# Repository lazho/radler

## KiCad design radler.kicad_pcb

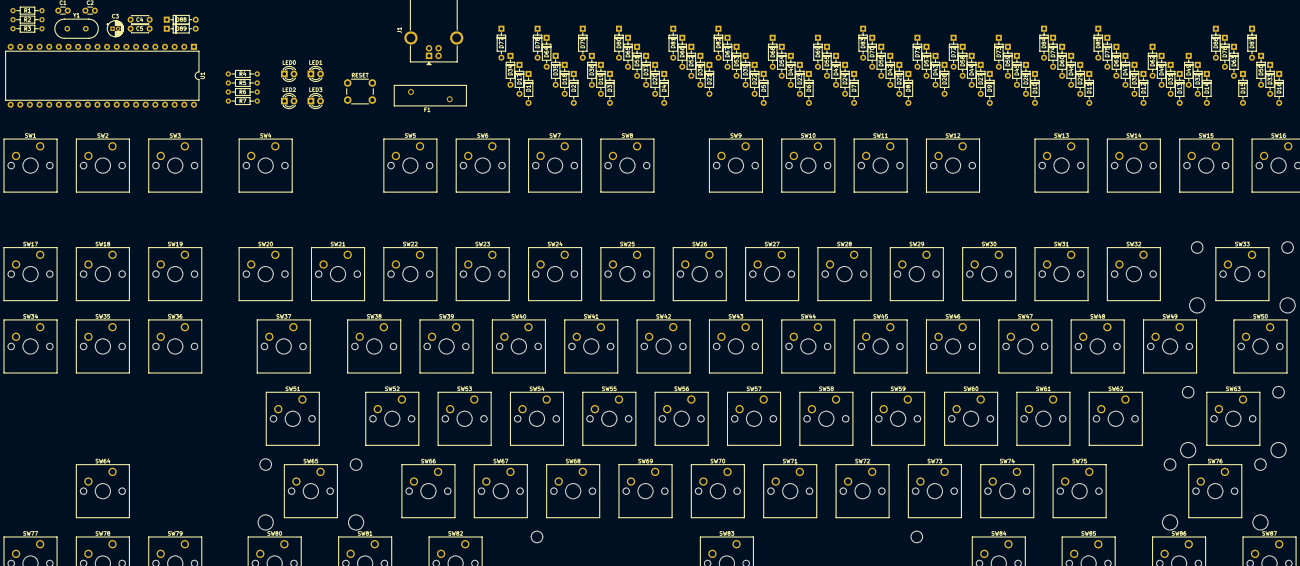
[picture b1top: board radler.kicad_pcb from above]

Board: 2 copper layers, 197 parts (0 on the bottom side), 128 nets, no tracks yet.

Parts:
C1, C2: 20p; C_Disc_D3.0mm_W1.6mm_P2.50mm
C3: 4.7u; CP_Radial_D4.0mm_P1.50mm
C4, C5: 0.1u; C_Disc_D4.3mm_W1.9mm_P5.00mm
D1, D2, D3, D4, D5, D6, D7, D8, D9, D10, D11, D12, D13, D14, D15, D16, D17, D18, D19, D20, D21, D22, D23, D24, D25, D26, D27, D28, D29, D30, D31, D32, D33, D34, D35, D36, D37, D38, D39, D40, D41, D42, D43, D44, D45, D46, D47, D48, D49, D50, D51, D52, D53, D54, D55, D56, D57, D58, D59, D60, D61, D62, D63, D64, D65, D66, D67, D68, D69, D70, D71, D72, D73, D74, D75, D76, D77, D78, D79, D80, D81, D82, D83, D84, D85, D86, D87: 1N4148; D_DO-35_SOD27_P7.62mm_Horizontal
D88, D89: 3.6V; D_DO-35_SOD27_P7.62mm_Horizontal
F1: 100mA; Fuse_BelFuse_0ZRE0100FF_L18.7mm_W5.1mm
J1: USB_B_Mini; USB_B_OST_USB-B1HSxx_Horizontal
LED0: A; LED_D3.0mm
LED1: B; LED_D3.0mm
LED2: C; LED_D3.0mm
LED3: D; LED_D3.0mm
R1, R4, R5, R6, R7: 1.5k; R_Axial_DIN0204_L3.6mm_D1.6mm_P7.62mm_Horizontal
R2, R3: 68; R_Axial_DIN0204_L3.6mm_D1.6mm_P7.62mm_Horizontal
RESET: RESET; SW_PUSH_6mm
SW1: Pause; SW_Cherry_MX_1.00u_PCB
SW2: ScrLk; SW_Cherry_MX_1.00u_PCB
SW3: PrtSc; SW_Cherry_MX_1.00u_PCB
SW4: Esc; SW_Cherry_MX_1.00u_PCB
SW5: F1; SW_Cherry_MX_1.00u_PCB
SW6: F2; SW_Cherry_MX_1.00u_PCB
SW7: F3; SW_Cherry_MX_1.00u_PCB
SW8: F4; SW_Cherry_MX_1.00u_PCB
SW9: F5; SW_Cherry_MX_1.00u_PCB
SW10: F6; SW_Cherry_MX_1.00u_PCB
SW11: F7; SW_Cherry_MX_1.00u_PCB
SW12: F8; SW_Cherry_MX_1.00u_PCB
SW13: F9; SW_Cherry_MX_1.00u_PCB
SW14: F10; SW_Cherry_MX_1.00u_PCB
SW15: F11; SW_Cherry_MX_1.00u_PCB
SW16: F12; SW_Cherry_MX_1.00u_PCB
SW17: PgUp; SW_Cherry_MX_1.00u_PCB
SW18: Home; SW_Cherry_MX_1.00u_PCB
SW19: Ins; SW_Cherry_MX_1.00u_PCB
SW20: `; SW_Cherry_MX_1.00u_PCB
SW21: 1; SW_Cherry_MX_1.00u_PCB
SW22: 2; SW_Cherry_MX_1.00u_PCB
SW23: 3; SW_Cherry_MX_1.00u_PCB
SW24: 4; SW_Cherry_MX_1.00u_PCB
SW25: 5; SW_Cherry_MX_1.00u_PCB
SW26: 6; SW_Cherry_MX_1.00u_PCB
SW27: 7; SW_Cherry_MX_1.00u_PCB
SW28: 8; SW_Cherry_MX_1.00u_PCB
SW29: 9; SW_Cherry_MX_1.00u_PCB
SW30: 0; SW_Cherry_MX_1.00u_PCB
SW31: -; SW_Cherry_MX_1.00u_PCB
SW32: =; SW_Cherry_MX_1.00u_PCB
SW33: Backspace; SW_Cherry_MX_2.00u_PCB
SW34: PgDn; SW_Cherry_MX_1.00u_PCB
SW35: End; SW_Cherry_MX_1.00u_PCB
SW36: Del; SW_Cherry_MX_1.00u_PCB
SW37: Tab; SW_Cherry_MX_1.50u_PCB
SW38: Q; SW_Cherry_MX_1.00u_PCB
SW39: W; SW_Cherry_MX_1.00u_PCB
SW40: E; SW_Cherry_MX_1.00u_PCB
SW41: R; SW_Cherry_MX_1.00u_PCB
SW42: T; SW_Cherry_MX_1.00u_PCB
SW43: Y; SW_Cherry_MX_1.00u_PCB
SW44: U; SW_Cherry_MX_1.00u_PCB
SW45: I; SW_Cherry_MX_1.00u_PCB
SW46: O; SW_Cherry_MX_1.00u_PCB
SW47: P; SW_Cherry_MX_1.00u_PCB
SW48: [; SW_Cherry_MX_1.00u_PCB
SW49: ]; SW_Cherry_MX_1.00u_PCB
SW50: \; SW_Cherry_MX_1.50u_PCB
SW51: CapsLock; SW_Cherry_MX_1.75u_PCB
SW52: A; SW_Cherry_MX_1.00u_PCB
SW53: S; SW_Cherry_MX_1.00u_PCB
SW54: D; SW_Cherry_MX_1.00u_PCB
SW55: F; SW_Cherry_MX_1.00u_PCB
SW56: G; SW_Cherry_MX_1.00u_PCB
SW57: H; SW_Cherry_MX_1.00u_PCB
SW58: J; SW_Cherry_MX_1.00u_PCB
SW59: K; SW_Cherry_MX_1.00u_PCB
SW60: L; SW_Cherry_MX_1.00u_PCB
SW61: ;; SW_Cherry_MX_1.00u_PCB
SW62: '; SW_Cherry_MX_1.00u_PCB
SW63: Enter; SW_Cherry_MX_2.25u_PCB
SW64: Up; SW_Cherry_MX_1.00u_PCB
SW65: LShift; SW_Cherry_MX_2.25u_PCB
SW66: Z; SW_Cherry_MX_1.00u_PCB
SW67: X; SW_Cherry_MX_1.00u_PCB
SW68: C; SW_Cherry_MX_1.00u_PCB
SW69: V; SW_Cherry_MX_1.00u_PCB
SW70: B; SW_Cherry_MX_1.00u_PCB
SW71: N; SW_Cherry_MX_1.00u_PCB
SW72: M; SW_Cherry_MX_1.00u_PCB
SW73: ,; SW_Cherry_MX_1.00u_PCB
SW74: .; SW_Cherry_MX_1.00u_PCB
SW75: /; SW_Cherry_MX_1.00u_PCB
SW76: RShift; SW_Cherry_MX_2.75u_PCB
SW77: Left; SW_Cherry_MX_1.00u_PCB
SW78: Down; SW_Cherry_MX_1.00u_PCB
SW79: Right; SW_Cherry_MX_1.00u_PCB
SW80, SW87: Ctrl; SW_Cherry_MX_1.25u_PCB
SW81, SW85: Super; SW_Cherry_MX_1.25u_PCB
SW82, SW84: Alt; SW_Cherry_MX_1.25u_PCB
SW83: Space; SW_Cherry_MX_6.25u_PCB
SW86: Menu; SW_Cherry_MX_1.25u_PCB
U1: ATmega32-16PU; DIP-40_W15.24mm
Y1: 16MHz; Crystal_HC49-4H_Vertical

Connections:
COL0: SW1.2, SW17.2, SW34.2, SW77.2, U1.21
COL1: SW2.2, SW18.2, SW35.2, SW64.2, SW78.2, U1.22
COL2: SW3.2, SW19.2, SW36.2, SW79.2, U1.23
COL3: SW4.2, SW20.2, SW37.2, SW51.2, SW65.2, SW80.2, U1.20
COL4: SW21.2, SW38.2, SW52.2, SW66.2, SW81.2, U1.19
COL5: SW5.2, SW22.2, SW39.2, SW53.2, SW67.2, SW82.2, U1.18
COL6: SW6.2, SW23.2, SW40.2, SW54.2, SW68.2, U1.17
COL7: SW7.2, SW24.2, SW41.2, SW55.2, SW69.2, U1.16
COL8: SW8.2, SW25.2, SW42.2, SW56.2, SW70.2, SW83.2, U1.15
COL9: SW26.2, SW43.2, SW57.2, SW71.2, U1.14
COL10: SW9.2, SW27.2, SW44.2, SW58.2, SW72.2, U1.8
COL11: SW10.2, SW28.2, SW45.2, SW59.2, SW73.2, U1.7
COL12: SW11.2, SW29.2, SW46.2, SW60.2, SW74.2, SW84.2, U1.6
COL13: SW12.2, SW30.2, SW47.2, SW61.2, SW75.2, SW85.2, U1.5
COL14: SW13.2, SW31.2, SW48.2, SW62.2, U1.4
COL15: SW14.2, SW32.2, SW49.2, U1.3
COL16: SW15.2, SW63.2, SW76.2, SW86.2, U1.2
COL17: SW16.2, SW33.2, SW50.2, SW87.2, U1.1
GND: C1.2, C2.2, C3.2, C4.2, C5.2, D88.2, D89.2, J1.4, LED0.1, LED1.1, LED2.1, LED3.1, RESET.2, U1.11, U1.31
LED0: R4.2, U1.38
LED1: R5.2, U1.37
LED2: R6.2, U1.36
LED3: R7.2, U1.35
unnamed: D1.2, SW1.1
unnamed: D2.2, SW2.1
unnamed: D3.2, SW3.1
unnamed: D4.2, SW4.1
unnamed: D5.2, SW5.1
unnamed: D6.2, SW6.1
unnamed: D7.2, SW7.1
unnamed: D8.2, SW8.1
unnamed: D9.2, SW9.1
unnamed: D10.2, SW10.1
unnamed: D11.2, SW11.1
unnamed: D12.2, SW12.1
unnamed: D13.2, SW13.1
unnamed: D14.2, SW14.1
unnamed: D15.2, SW15.1
unnamed: D16.2, SW16.1
unnamed: D17.2, SW17.1
unnamed: D18.2, SW18.1
unnamed: D19.2, SW19.1
unnamed: D20.2, SW20.1
unnamed: D21.2, SW21.1
unnamed: D22.2, SW22.1
unnamed: D23.2, SW23.1
unnamed: D24.2, SW24.1
unnamed: D25.2, SW25.1
unnamed: D26.2, SW26.1
unnamed: D27.2, SW27.1
unnamed: D28.2, SW28.1
unnamed: D29.2, SW29.1
unnamed: D30.2, SW30.1
unnamed: D31.2, SW31.1
unnamed: D32.2, SW32.1
unnamed: D33.2, SW33.1
unnamed: D34.2, SW34.1
unnamed: D35.2, SW35.1
unnamed: D36.2, SW36.1
unnamed: D37.2, SW37.1
unnamed: D38.2, SW38.1
unnamed: D39.2, SW39.1
unnamed: D40.2, SW40.1
unnamed: D41.2, SW41.1
unnamed: D42.2, SW42.1
unnamed: D43.2, SW43.1
unnamed: D44.2, SW44.1
unnamed: D45.2, SW45.1
unnamed: D46.2, SW46.1
unnamed: D47.2, SW47.1
unnamed: D48.2, SW48.1
unnamed: D49.2, SW49.1
unnamed: D50.2, SW50.1
unnamed: D51.2, SW51.1
unnamed: D52.2, SW52.1
unnamed: D53.2, SW53.1
unnamed: D54.2, SW54.1
unnamed: D55.2, SW55.1
unnamed: D56.2, SW56.1
unnamed: D57.2, SW57.1
unnamed: D58.2, SW58.1
unnamed: D59.2, SW59.1
unnamed: D60.2, SW60.1
unnamed: D61.2, SW61.1
unnamed: D62.2, SW62.1
unnamed: D63.2, SW63.1
unnamed: D64.2, SW64.1
unnamed: D65.2, SW65.1
unnamed: D66.2, SW66.1
unnamed: D67.2, SW67.1
unnamed: D68.2, SW68.1
unnamed: D69.2, SW69.1
unnamed: D70.2, SW70.1
unnamed: D71.2, SW71.1
unnamed: D72.2, SW72.1
unnamed: D73.2, SW73.1
unnamed: D74.2, SW74.1
unnamed: D75.2, SW75.1
unnamed: D76.2, SW76.1
unnamed: D77.2, SW77.1
unnamed: D78.2, SW78.1
unnamed: D79.2, SW79.1
unnamed: D80.2, SW80.1
unnamed: D81.2, SW81.1
unnamed: D82.2, SW82.1
unnamed: D83.2, SW83.1
unnamed: D84.2, SW84.1
unnamed: D85.2, SW85.1
unnamed: D86.2, SW86.1
unnamed: D87.2, SW87.1
unnamed: D88.1, J1.3, R2.1
unnamed: D89.1, J1.2, R1.2, R3.2
unnamed: F1.2, J1.1
unnamed: LED0.2, R4.1
unnamed: LED1.2, R5.1
unnamed: LED2.2, R6.1
unnamed: LED3.2, R7.1
RESET: C3.1, C4.1, C5.1, F1.1, R1.1, RESET.1, U1.9, U1.10, U1.30
ROW0: D1.1, D2.1, D3.1, D4.1, D5.1, D6.1, D7.1, D8.1, D9.1, D10.1, D11.1, D12.1, D13.1, D14.1, D15.1, D16.1, U1.24
ROW1: D17.1, D18.1, D19.1, D20.1, D21.1, D22.1, D23.1, D24.1, D25.1, D26.1, D27.1, D28.1, D29.1, D30.1, D31.1, D32.1, D33.1, U1.25
ROW2: D34.1, D35.1, D36.1, D37.1, D38.1, D39.1, D40.1, D41.1, D42.1, D43.1, D44.1, D45.1, D46.1, D47.1, D48.1, D49.1, D50.1, U1.26
ROW3: D51.1, D52.1, D53.1, D54.1, D55.1, D56.1, D57.1, D58.1, D59.1, D60.1, D61.1, D62.1, D63.1, U1.27
ROW4: D64.1, D65.1, D66.1, D67.1, D68.1, D69.1, D70.1, D71.1, D72.1, D73.1, D74.1, D75.1, D76.1, U1.28
ROW5: D77.1, D78.1, D79.1, D80.1, D81.1, D82.1, D83.1, D84.1, D85.1, D86.1, D87.1, U1.29
USB_D+: R2.2, U1.39
USB_D-: R3.1, U1.40
XTAL1: C1.1, U1.13, Y1.1
XTAL2: C2.1, U1.12, Y1.2

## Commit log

2019-08-02 organize pcb and schematic
